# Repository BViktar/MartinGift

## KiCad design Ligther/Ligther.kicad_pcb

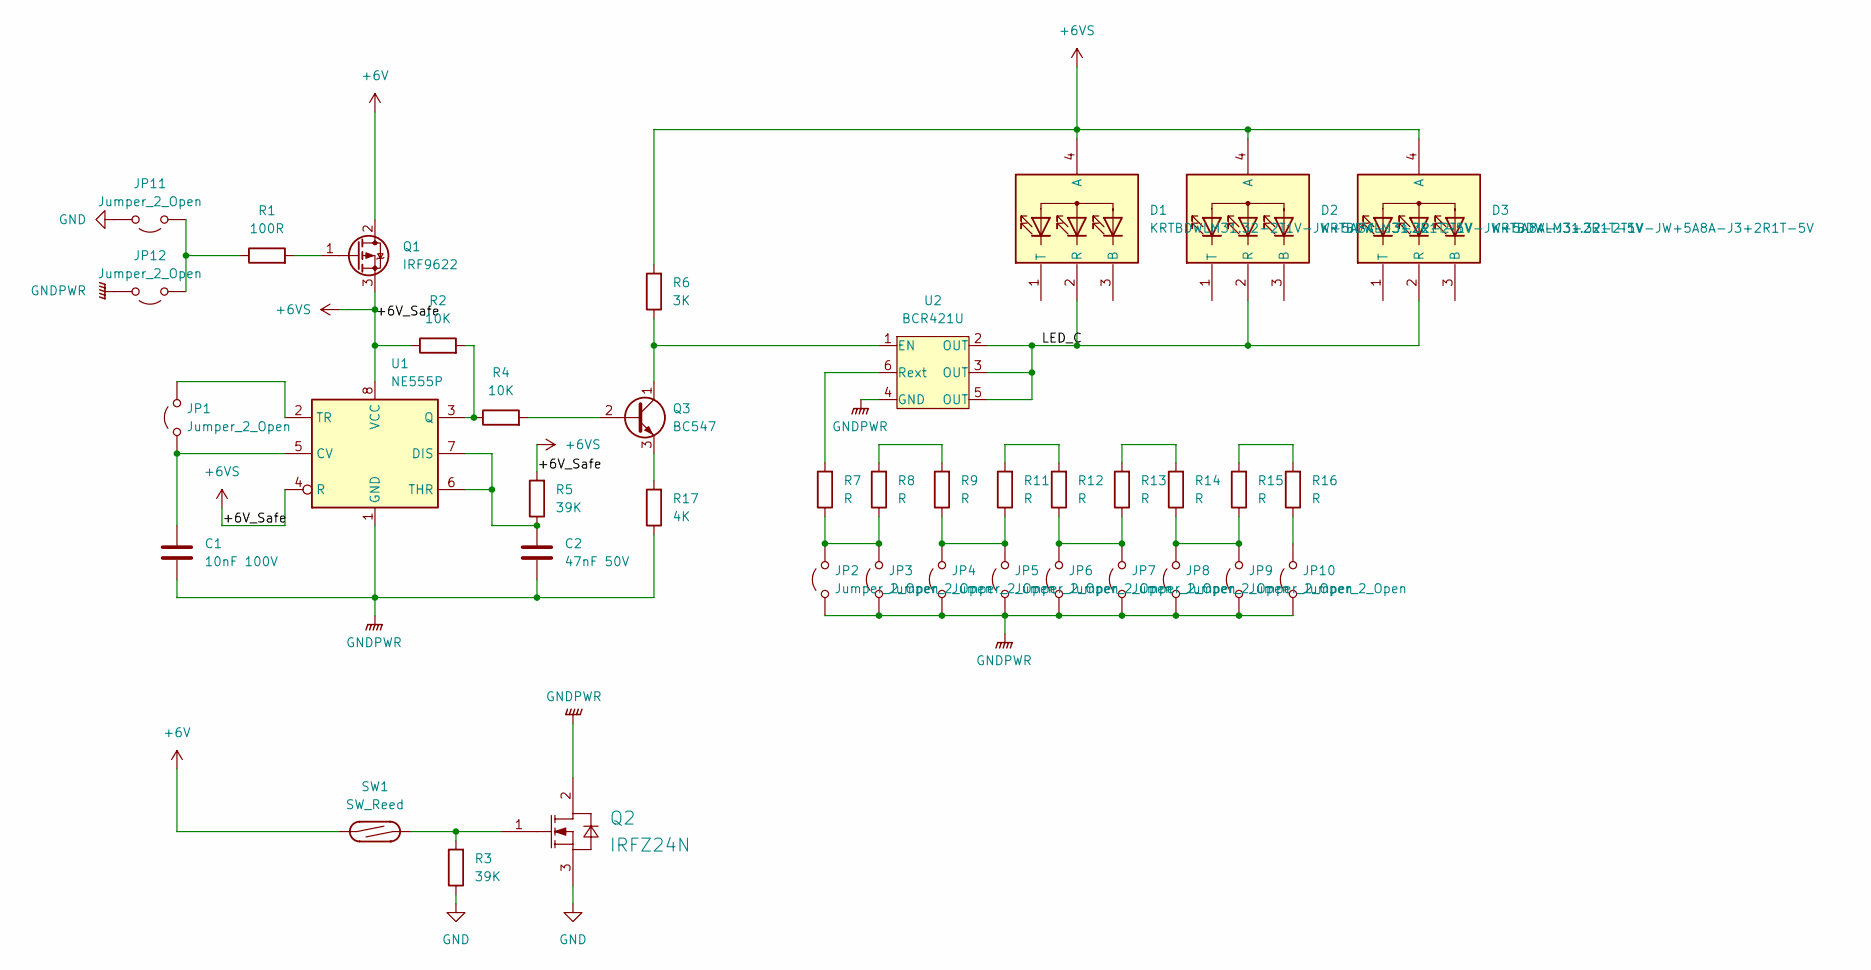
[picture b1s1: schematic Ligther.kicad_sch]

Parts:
C1: 10nF 100V; C_Disc_D3.4mm_W2.1mm_P2.50mm
C2: 47nF 50V; C_Disc_D4.3mm_W1.9mm_P5.00mm
D1, D2, D3: KRTBDWLM31.32-2T1V-JW+5A8A-J3+2R1T-5V; KRTBDWLM3132T4U6JWAAABJ3R4S65V; Manufacturer_Part_Number KRTBDWLM31.32-2T1V-JW+5A8A-J3+2R1T-5V; Mouser Part Number 720-31322T1VJW5A8A
JP1, JP2, JP3, JP4, JP5, JP6, JP7, JP8, JP9, JP10, JP11, JP12: Jumper_2_Open; PinHeader_2x01_P1.27mm_Vertical
Q1: IRF9622; TO-220-3_Vertical
Q2: IRFZ24N; TO-220-3_Vertical
Q3: BC547; TO-92_Inline
R1: 100R; R_Axial_DIN0207_L6.3mm_D2.5mm_P10.16mm_Horizontal
R2, R4: 10K; R_Axial_DIN0207_L6.3mm_D2.5mm_P10.16mm_Horizontal
R3, R5: 39K; R_Axial_DIN0207_L6.3mm_D2.5mm_P10.16mm_Horizontal
R6: 3K; R_Axial_DIN0207_L6.3mm_D2.5mm_P10.16mm_Horizontal
R7, R8, R9, R11, R12, R13, R14, R15, R16: R; R_Axial_DIN0207_L6.3mm_D2.5mm_P10.16mm_Horizontal
R17: 4K; R_Axial_DIN0207_L6.3mm_D2.5mm_P10.16mm_Horizontal
SW1: SW_Reed; R_Axial_DIN0207_L6.3mm_D2.5mm_P10.16mm_Horizontal
U1: NE555P; DIP-8_W7.62mm
U2: BCR421U; SC-74-6_1.55x2.9mm_P0.95mm

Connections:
+6V: Q1.2 (D), SW1.1
+6VS: D1.4 (A), D2.4 (A), D3.4 (A), Q1.3 (S), R2.1, R5.2, R6.2, U1.4 (R), U1.8 (VCC)
/LED_C: D1.2 (R), D2.2 (R), D3.2 (R), U2.2 (OUT), U2.3 (OUT), U2.5 (OUT)
GND: JP11.2 (B), Q2.3 (SOURCE), R3.1; also elsewhere on the board
GNDPWR: C1.2, C2.2, JP2.1 (A), JP3.1 (A), JP4.1 (A), JP5.1 (A), JP6.1 (A), JP7.1 (A), JP8.1 (A), JP9.1 (A), JP10.1 (A), JP12.2 (B), Q2.2 (DRAIN), R17.1, U1.1 (GND), U2.4 (GND); also elsewhere on the board
unnamed: C1.1, JP1.1 (A), U1.5 (CV)
unnamed: JP1.2 (B), U1.2 (TR)
unnamed: JP2.2 (B), JP3.2 (B), R7.1, R8.1
unnamed: JP4.2 (B), JP5.2 (B), R9.1, R11.1
unnamed: JP6.2 (B), JP7.2 (B), R12.1, R13.1
unnamed: JP8.2 (B), JP9.2 (B), R14.1, R15.1
unnamed: JP10.2 (B), R16.1
unnamed: JP11.1 (A), JP12.1 (A), R1.1
unnamed: Q1.1 (G), R1.2
unnamed: Q2.1 (GATE), R3.2, SW1.2
unnamed: Q3.2 (B), R4.2
unnamed: Q3.1 (C), R6.1, U2.1 (EN)
unnamed: Q3.3 (E), R17.2
unnamed: R8.2, R9.2
unnamed: R11.2, R12.2
unnamed: R13.2, R14.2
unnamed: R15.2, R16.2
unnamed: C2.1, R5.1, U1.6 (THR), U1.7 (DIS)
unnamed: R2.2, R4.1, U1.3 (Q)
unnamed: R7.2, U2.6 (Rext)

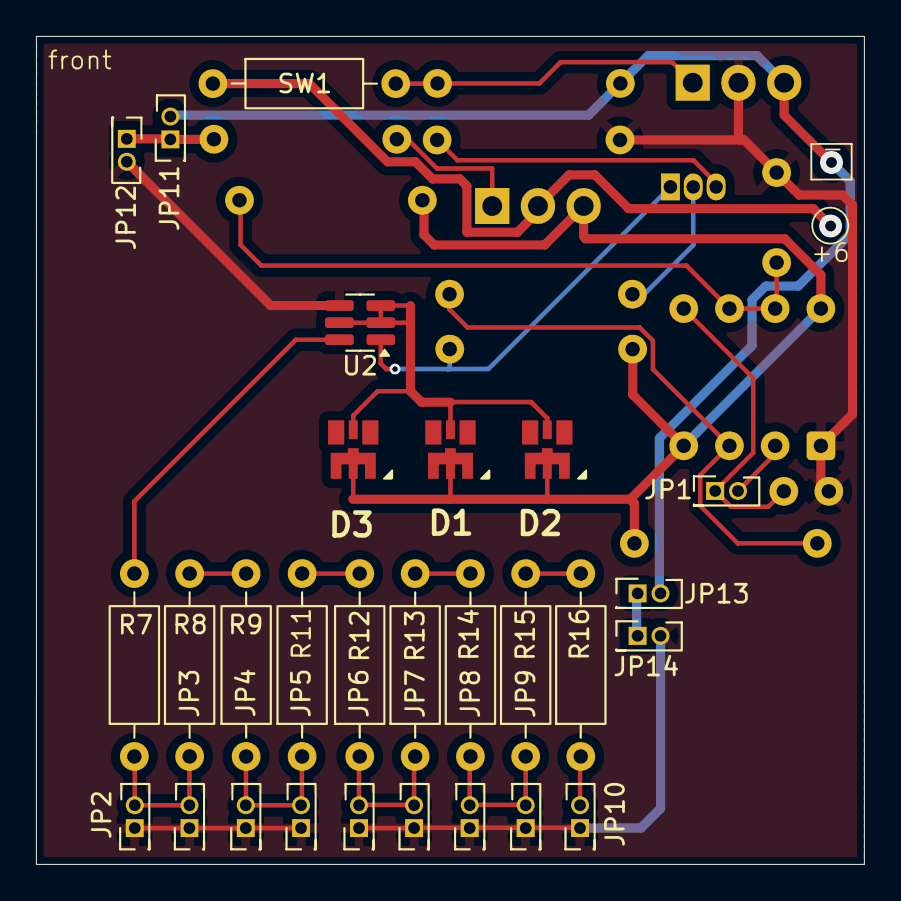
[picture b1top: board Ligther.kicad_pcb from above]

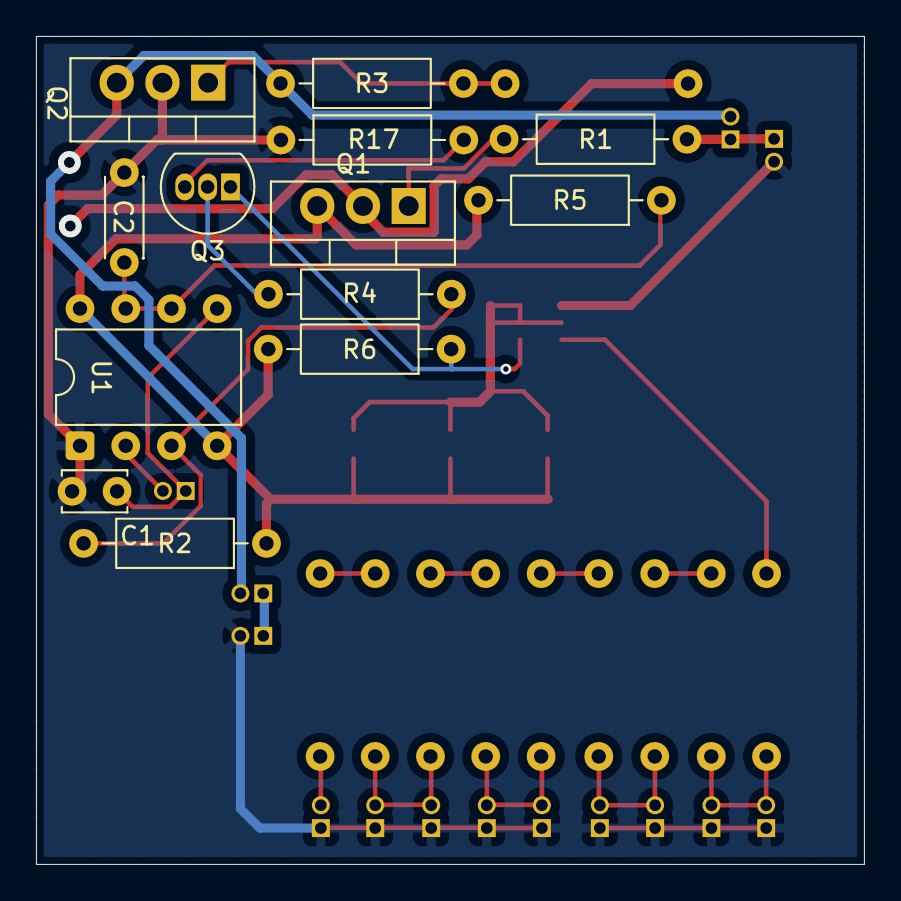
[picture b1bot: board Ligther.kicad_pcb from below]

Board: 2 copper layers, 46.0 x 46.0 mm, 41 parts (13 on the bottom side), 26 nets.

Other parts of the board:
JP13, JP14: Jumper_2_Open; PinHeader_2x01_P1.27mm_Vertical

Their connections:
GND: JP13.2 (B); also elsewhere on the board
GNDPWR: JP14.2 (B); also elsewhere on the board
unnamed: JP13.1 (A), JP14.1 (A)

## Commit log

2025-07-13 Add chassis
2025-07-14 Add tyre spike
2025-07-18 Add pcb and production files
